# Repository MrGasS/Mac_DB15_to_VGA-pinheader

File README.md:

# Mac DB15 to VGA - Pin Header version by MrGasS aka S.E.M.M.

This is a classic Macintosh DB15 video out to VGA adapter. It's uses the same dip switch settings as the Sony MacView and Unimac 82D.  
CUSTOMIZED FOR PIN HEADERS BY MRGASS AKA S.E.M.M.

[Dip Switch Settings](docs/manuals)

## Bill of Materials

| Quantity | Description                | Designators            | Product Number   | Datasheet                                                    |
| :------- | -------------------------- | ---------------------- | ---------------- | ------------------------------------------------------------ |
| 1        | DB15                       | J1                     | A-DS 15 A/KG-T4S | [pdf](docs/datasheets/J1_ASS_4888_CO.pdf)                    |
| 1        | HD15                       | J2                     | HD15-SN-25       | [pdf](docs/datasheets/J2_hdxx-sn-25-data-sheet.pdf)          |
| -        | 2.54mm pin headers         | SWA1, SWB1             | -                | [pdf](docs/datasheets/PinHeaderDatasheet-C0CKB1G.jpg)        |
| 6        | Diode 1N4148 DO-35         | D1, D2, D3, D4, D5, D6 | 1N4148           | [pdf](docs/datasheets/D1_D2_D3_D4_D5_D6_1N914_D-2309448.pdf) |

## License

This work is licensed under a <a rel="license" href="http://creativecommons.org/licenses/by-nc-sa/4.0/">Creative Commons Attribution-NonCommercial-ShareAlike 4.0 International License</a>.

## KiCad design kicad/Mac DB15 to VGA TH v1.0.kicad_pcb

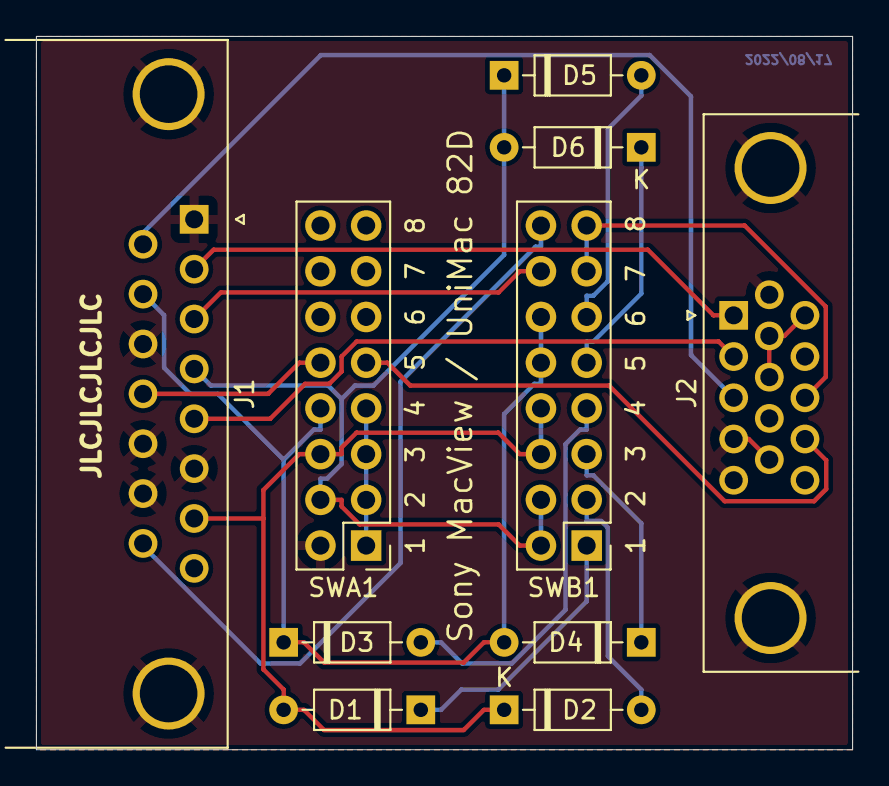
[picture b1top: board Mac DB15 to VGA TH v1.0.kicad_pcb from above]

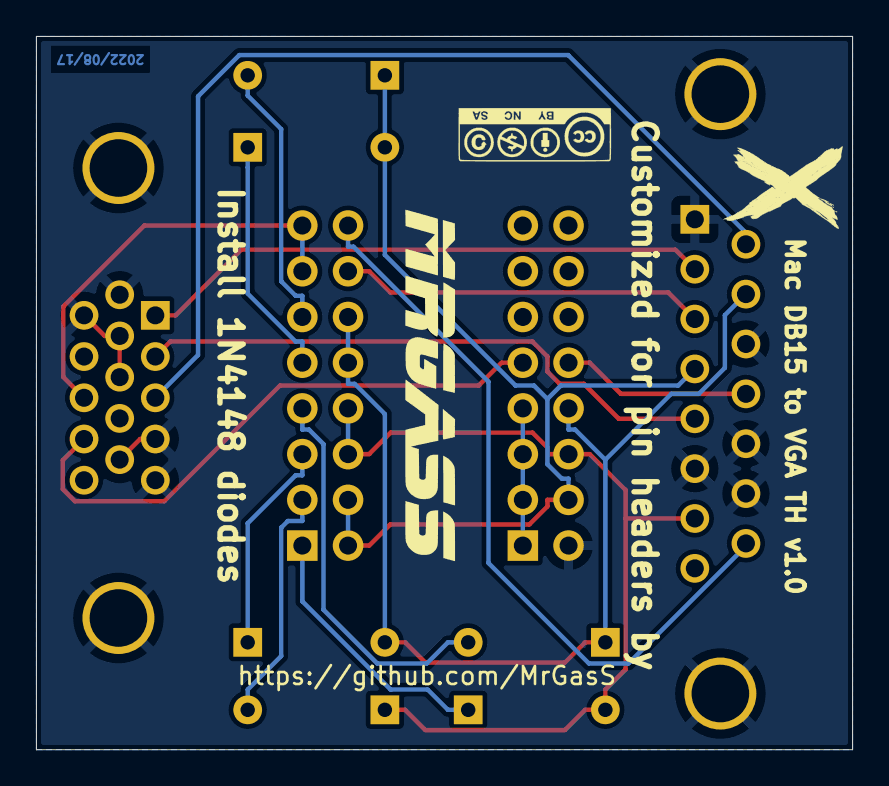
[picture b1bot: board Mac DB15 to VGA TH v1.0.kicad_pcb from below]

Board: 2 copper layers, 45.3 x 39.6 mm, 13 parts (2 on the bottom side), 19 nets.

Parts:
D1, D2, D3, D4, D5, D6: 1N4148; D_DO-35_SOD27_P7.62mm_Horizontal
J1: Mac_DB15_Male_MountingHoles; DSUB-15_Male_Horizontal_P2.77x2.84mm_EdgePinOffset7.70mm_Ho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
J2: VGA_DB15_Female_HighDensity_MountingHoles; DSUB-15-HD_Female_Horizontal_P2.29x1.98mm_EdgePinOffset3.03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
LOGO: LOGO; cc_by_nc_sa_front_silk_screen
LOGOX: LOGO; logo_7_back
SWA1: SW_DIP_x08; PinHeader_2x08_P2.54mm_Vertical
SWB1: SW_DIP_x08; PinHeader_2x08_P2.54mm_Vertical
mrgasslogo: LOGO; mrgasslogo

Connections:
/B: J1.9, J2.3
/CS: J1.3, SWB1.10
/D1: D1.1, SWB1.1
/D2: D2.2, SWB1.2
/D3: D3.2, SWB1.4
/D4: D4.1, SWB1.3
/D5: D5.2, SWB1.6
/D6: D6.1, SWB1.5
/G: J1.5, J2.2
/GND: J1.0, J1.1, J1.6, J1.11, J1.13, J1.14, J2.0, J2.4, J2.5, J2.6, J2.7, J2.8, J2.10, J2.11, SWA1.16
/HS: J1.15, SWB1.9
/HS-CS: J2.13, SWB1.7, SWB1.8
/R: J1.2, J2.1
/S0-1: D5.1, D6.2, J1.4, SWA1.15, SWB1.15, SWB1.16
/S1-1: D1.2, D2.1, J1.7, SWA1.14, SWB1.13, SWB1.14
/S2-1: D3.1, D4.2, J1.10, SWA1.13, SWB1.11, SWB1.12
/VS: J1.12, SWA1.12
/VS-2: J2.14, SWA1.5
unnamed: SWA1.1, SWA1.2, SWA1.3, SWA1.4
